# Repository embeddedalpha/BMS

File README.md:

# BMS
Battery Management System for 6s Li-ion Pack

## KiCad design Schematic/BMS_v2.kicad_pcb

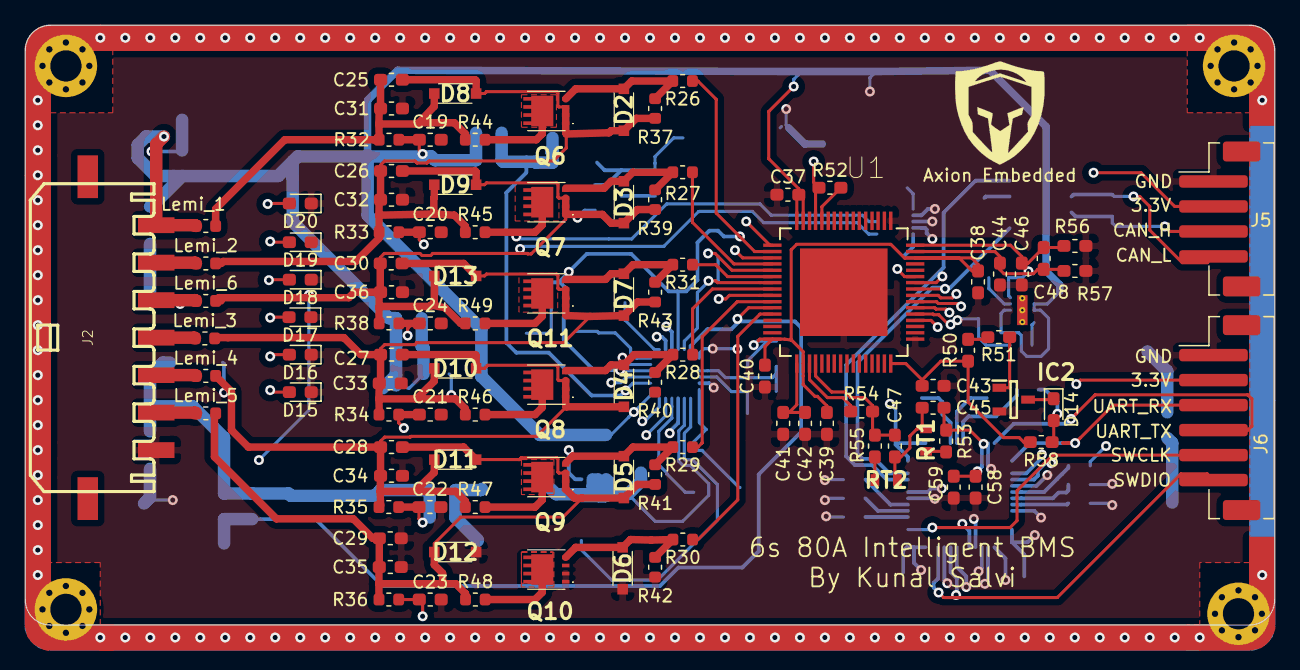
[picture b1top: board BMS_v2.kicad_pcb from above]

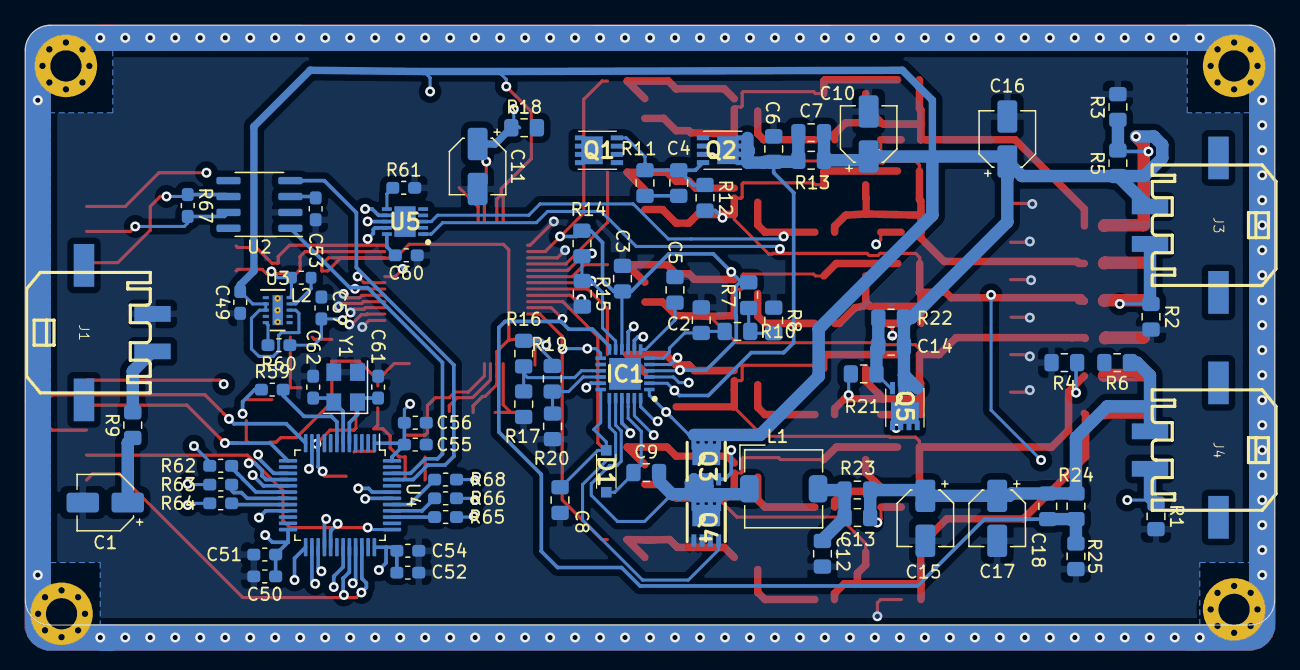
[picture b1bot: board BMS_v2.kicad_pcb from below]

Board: 4 copper layers, 100.0 x 48.0 mm, 185 parts (82 on the bottom side), 119 nets.

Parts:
C1: CP1; CP_Elec_4x3.9
C2, C7, C12, C13, C14: 0.1U; C_0805_2012Metric_Pad1.15x1.40mm_HandSolder
C3, C8: 1U; C_0805_2012Metric_Pad1.15x1.40mm_HandSolder
C4: 0.1u; C_0805_2012Metric_Pad1.15x1.40mm_HandSolder
C5: 0.056U; C_0805_2012Metric_Pad1.15x1.40mm_HandSolder
C6: C_Small; C_0805_2012Metric_Pad1.15x1.40mm_HandSolder
C9, C18: 22P; C_0805_2012Metric_Pad1.15x1.40mm_HandSolder
C10, C15, C16, C17: 10U; CP_Elec_4x3.9
C11: 1U; CP_Elec_4x3.9
C19, C20, C21, C22, C23, C24, C25, C26, C27, C28, C29, C30, C37, C39, C42, C48: 0.1U; C_0603_1608Metric_Pad1.05x0.95mm_HandSolder
C31, C32, C33, C34, C35, C36: 3300P; C_0603_1608Metric_Pad1.05x0.95mm_HandSolder
C38, C41, C43, C49, C53: 2.2U; C_0603_1608Metric_Pad1.05x0.95mm_HandSolder
C40, C45, C47: 0.047U; C_0603_1608Metric_Pad1.05x0.95mm_HandSolder
C44, C46: 1U; C_0603_1608Metric_Pad1.05x0.95mm_HandSolder
C50, C52, C55, C58: 0.47U; C_0603_1608Metric_Pad1.05x0.95mm_HandSolder
C51, C54, C56, C59, C60, C61, C62: 10N; C_0603_1608Metric_Pad1.05x0.95mm_HandSolder
C57: 22U; C_0603_1608Metric_Pad1.05x0.95mm_HandSolder
D1: D_Schottky; BZT52B5V1E308
D2, D3, D4, D5, D6, D7, D8, D9, D10, D11, D12, D13: BZT52B5V1-E3-08; BZT52B5V1E308
D14, D15, D16, D17, D18, D19, D20: LED; LED_0603_1608Metric_Pad1.05x0.95mm_HandSolder
IC1: BQ24610RGER; QFN50P400X400X100-25N-D
IC2: FDN359AN; SOT95P251X112-3N
J1: CHARGER; 43650-0212
J2: Conn_01x07; 43650-0712
J3: SYSTEM; 43650-0212
J4: BATTERY; 43650-0212
J5: Conn_01x04; JST_PH_B4B-PH-SM4-TB_1x04-1MP_P2.00mm_Vertical
J6: Conn_01x06; JST_PH_B6B-PH-SM4-TB_1x06-1MP_P2.00mm_Vertical
L1: 6.8U; L_TDK_SLF6025
L2: 6.8U; L_0603_1608Metric
Lemi_1, Lemi_2, Lemi_3, Lemi_4, Lemi_5, Lemi_6: 500; R_0603_1608Metric
Q1, Q2, Q5: SI7617DN-T1-GE3; SIS862DNT1GE3
Q3, Q4: SIS412DN-T1-GE3; POWERPAK-1212-8
Q6, Q7, Q8, Q9, Q10, Q11: CSD18543Q3AT
R1, R2, R3, R4, R5, R6: R; R_0805_2012Metric_Pad1.15x1.40mm_HandSolder
R7: 9.31K; R_0805_2012Metric_Pad1.15x1.40mm_HandSolder
R8: 430K; R_0805_2012Metric_Pad1.15x1.40mm_HandSolder
R9, R11: 100k; R_0805_2012Metric_Pad1.15x1.40mm_HandSolder
R10, R14, R15, R16, R17, R19, R20, R22, R25: 100K; R_0805_2012Metric_Pad1.15x1.40mm_HandSolder
R12, R21: 1K; R_0805_2012Metric_Pad1.15x1.40mm_HandSolder
R13: 0.01; R_0805_2012Metric_Pad1.15x1.40mm_HandSolder
R18: 10; R_0805_2012Metric_Pad1.15x1.40mm_HandSolder
R23: 0.010; R_0805_2012Metric_Pad1.15x1.40mm_HandSolder
R24: 500K; R_0805_2012Metric_Pad1.15x1.40mm_HandSolder
R26, R27, R28, R29, R30, R31, R32, R33, R34, R35, R36, R38: 1K; R_0603_1608Metric
R37, R39, R40, R41, R42, R43: 1M; R_0603_1608Metric
R44, R45, R46, R47, R48, R49: R; R_0603_1608Metric
R50: 100K; R_0603_1608Metric_Pad1.05x0.95mm_HandSolder
R51: 100; R_0603_1608Metric_Pad1.05x0.95mm_HandSolder
R52, R54: 1.82K; R_0603_1608Metric_Pad1.05x0.95mm_HandSolder
R53, R55: 1.47K; R_0603_1608Metric_Pad1.05x0.95mm_HandSolder
R56, R57: 0; R_0603_1608Metric_Pad1.05x0.95mm_HandSolder
R58: 2.7K; R_0603_1608Metric_Pad1.05x0.95mm_HandSolder
R59, R61: 100k; R_0603_1608Metric_Pad1.05x0.95mm_HandSolder
R60, R62, R63, R64, R65, R66, R68: 1K; R_0603_1608Metric_Pad1.05x0.95mm_HandSolder
R67: 120; R_0603_1608Metric_Pad1.05x0.95mm_HandSolder
RT1, RT2: NTCG163JF103FT1; THRMC1608X90N
U1: BQ76PL536A; QFP50P1200X1200X120-65N
U2: TCAN332; SOIC-8_3.9x4.9mm_P1.27mm
U3: TPS62177DQC; WSON-10-1EP_2x3mm_P0.5mm_EP0.84x2.4mm_ThermalVias
U4: STM32F103C8Tx; LQFP-48_7x7mm_P0.5mm
U5: PAC1720-1-AIA-TR; SON50P300X300X90-11N-D
Y1: 8MHz; Crystal_SMD_SeikoEpson_FA238V-4Pin_3.2x2.5mm

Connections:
+3V3: C50.1, C51.1, C52.1, C53.2, C54.1, C55.1, C56.1, C57.2, C58.1, C59.1, C60.2, J5.2, J6.2, L2.2, R59.1, R60.1, U2.3, U3.10, U4.1, U4.9, U4.24, U4.36, U4.48, U5.10
/Balance Module/ALERT: U1.38, U4.26
/Balance Module/CB1: R30.1, U1.12
/Balance Module/CB2: R29.1, U1.10
/Balance Module/CB3: R28.1, U1.8
/Balance Module/CB4: R31.1, U1.6
/Balance Module/CB5: R27.1, U1.4
/Balance Module/CB6: R26.1, U1.2
/Balance Module/CONV: U1.36, U4.27
/Balance Module/CS: U1.43, U4.29
/Balance Module/DRDY: U1.37, U4.25
/Balance Module/FAULT: U1.39, U4.28
/Balance Module/SCLK: U1.40, U4.15
/Balance Module/SDI: U1.42, U4.17
/Balance Module/SDO: U1.41, U4.16
/Balance Module/VC1: C23.1, R36.2, U1.11
/Balance Module/VC2: C22.1, R35.2, U1.9
/Balance Module/VC3: C21.1, R34.2, U1.7
/Balance Module/VC4: C24.1, R38.2, U1.5
/Balance Module/VC5: C20.1, R33.2, U1.3
/Balance Module/VC6: C19.1, R32.2, U1.1
/Cell_AFE/BAT1: J2.2, Lemi_5.1
/Cell_AFE/BAT2: J2.3, Lemi_4.1
/Cell_AFE/BAT3: J2.4, Lemi_3.1
/Cell_AFE/BAT4: J2.5, Lemi_6.1
/Cell_AFE/BAT5: J2.6, Lemi_2.1
/Charger/PG: IC1.8, U4.31
/Charger/Power_IN: J1.1, Q1.5, Q1.6, Q1.7, Q1.8, R9.2
/Charger/STAT1: IC1.5, U4.32
/Charger/STAT2: IC1.9, U4.33
/Charger/THERMO: R7.1, R8.2, R10.1
/Controller/BAT_R_+: J4.2, R1.1, U5.3
/Controller/BAT_V: R4.1, R6.2, U4.10
/Controller/SYS_R_+: J3.2, R2.1, U5.1
/Controller/SYS_V: R3.1, R5.2, U4.11
ACDRV: IC1.3, R12.2
ACN: C7.1, C10.1, C13.1, C14.2, C15.1, C16.1, C17.1, C18.2, C37.2, C49.2, IC1.1, IC1.13, J2.7, J3.1, J4.1, Lemi_1.1, Q3.5, Q3.6, Q3.7, Q3.8, Q5.1, Q5.2, Q5.3, Q5.5, Q5.6, Q5.7, Q5.8, R5.1, R6.1, R13.1, R22.2, R23.1, R24.2, U1.63, U1.64, U3.2, U3.3, U3.8
ACP: C6.2, C7.2, IC1.2, IC1.17, Q2.5, Q2.6, Q2.7, Q2.8, R13.2
ACSET: IC1.16, R19.2, R20.1
BATDRV: IC1.23, R21.2
BTST: C9.1, D1.1, IC1.22
CANRX: U2.4, U4.45
CANTX: U2.1, U4.46
CAN_H: J5.3, R67.2, U2.7
CAN_L: J5.4, R67.1, U2.6
CE: C3.1, C38.2, C39.2, C40.2, IC1.4, IC1.10, R7.2, R14.1, R16.1, R19.1, U1.16, U1.18, U1.46
GND: C1.2, C2.2, C3.2, C5.2, C6.1, C8.2, C10.2, C11.2, C12.2, C15.2, C16.2, C17.2, C19.2, C20.2, C21.2, C22.2, C23.2, C24.2, C29.2, C31.2, C32.2, C33.2, C34.2, C35.2, C36.2, C37.1, C38.1, C39.1, C40.1, C41.1, C42.1, C43.2, C44.2, C46.2, C49.1, C50.2, C51.2, C52.2, C53.1, C54.2, C55.2, C56.2, C57.1, C58.2, C59.2, C60.1, C61.2, C62.2, D6.2, D12.2, D15.1, D16.1, D17.1, D18.1, D19.1, D20.1, IC2.2, J1.2, J2.1, J5.1, J6.1, Q4.1, Q4.2, Q4.3, Q10.1, Q10.2, Q10.3, R1.2, R2.2, R3.2, R4.2, R8.1, R15.2, R17.2, R20.2, R25.1, R42.1, R56.1, R57.1, R61.2, U1.13, U1.14, U1.15, U1.25, U1.33, U1.34, U1.35, U1.44, U1.49, U1.50, U1.65, U2.2, U3.1, U3.4, U3.6, U3.7, U3.11, U4.8, U4.23, U4.35, U4.44, U4.47, U5.2, U5.4, U5.5, U5.11, Y1.2, Y1.3
GPAI+: C46.1, C48.1, R56.2, U1.48
GPAI-: C44.1, C48.2, R57.2, U1.47
GPIO: R50.2, R51.1, U1.45
HIDRV: IC1.21, Q3.4
I2C_ALERT: U4.21, U5.7
I2C_SCL: U4.42, U5.9
I2C_SDA: U4.43, U5.8
ISET1: IC1.11, R14.2, R15.1
ISET2: IC1.15, R16.2, R17.1
LDOA: C41.2, C42.2, U1.17
LED1: R62.2, U4.18
LED2: R63.2, U4.19
LED3: R64.2, U4.20
LED4: R65.2, U4.39
LED5: R66.2, U4.40
LED6: R68.2, U4.41
LODRV: IC1.19, Q4.4
unnamed: C1.1, R9.1
unnamed: C4.1, Q1.4, Q2.4, R11.1, R12.1
unnamed: C4.2, Q1.1, Q1.2, Q1.3, Q2.1, Q2.2, Q2.3, R11.2, R18.2
unnamed: C14.1, Q5.4, R21.1, R22.1
unnamed: C25.1, C31.1, D8.1, Lemi_1.2, R32.1, R44.1
unnamed: C25.2, C26.1, C32.1, D2.2, D8.2, D9.1, Lemi_2.2, Q6.1, Q6.2, Q6.3, R33.1, R37.1, R45.1
unnamed: C26.2, C30.1, C36.1, D3.2, D9.2, D13.1, Lemi_6.2, Q7.1, Q7.2, Q7.3, R38.1, R39.1, R49.1
unnamed: C27.1, C30.2, C33.1, D7.2, D10.1, D13.2, Lemi_3.2, Q11.1, Q11.2, Q11.3, R34.1, R43.1, R46.1
unnamed: C27.2, C28.1, C34.1, D4.2, D10.2, D11.1, Lemi_4.2, Q8.1, Q8.2, Q8.3, R35.1, R40.1, R47.1
unnamed: C28.2, C29.1, C35.1, D5.2, D11.2, D12.1, Lemi_5.2, Q9.1, Q9.2, Q9.3, R36.1, R41.1, R48.1
unnamed: D2.1, Q6.4, R26.2, R37.2
unnamed: D3.1, Q7.4, R27.2, R39.2
unnamed: D4.1, Q8.4, R28.2, R40.2
unnamed: D5.1, Q9.4, R29.2, R41.2
unnamed: D6.1, Q10.4, R30.2, R42.2
unnamed: D7.1, Q11.4, R31.2, R43.2
unnamed: D14.1, IC2.3
unnamed: D14.2, R58.1
unnamed: D15.2, R62.1
unnamed: D16.2, R63.1
unnamed: D17.2, R64.1
unnamed: D18.2, R65.1
unnamed: D19.2, R66.1
unnamed: D20.2, R68.1
unnamed: IC2.1, R51.2
unnamed: L2.1, U3.9
unnamed: Q6.5, Q6.6, Q6.7, Q6.8, Q6.9, R44.2
unnamed: Q7.5, Q7.6, Q7.7, Q7.8, Q7.9, R45.2
unnamed: Q8.5, Q8.6, Q8.7, Q8.8, Q8.9, R46.2
unnamed: Q9.5, Q9.6, Q9.7, Q9.8, Q9.9, R47.2
unnamed: Q10.5, Q10.6, Q10.7, Q10.8, Q10.9, R48.2
unnamed: Q11.5, Q11.6, Q11.7, Q11.8, Q11.9, R49.2
unnamed: R53.1, RT1.2
unnamed: R55.1, RT2.2
unnamed: R59.2, U4.7
unnamed: R60.2, U3.5
unnamed: R61.1, U5.6
OSC_IN: C61.1, U4.5, Y1.1
OSC_OUT: C62.1, U4.6, Y1.4
PH: C9.2, IC1.20, L1.1, Q3.1, Q3.2, Q3.3, Q4.5, Q4.6, Q4.7, Q4.8
REG50: C43.1, C45.1, C47.1, R50.1, R58.2, RT1.1, RT2.1, U1.32
REGN: C8.1, D1.2, IC1.18
SRP: C12.1, C13.2, IC1.14, L1.2, R23.2
SWCLK: J6.5, U4.37
SWDIO: J6.6, U4.34
TS: C2.1, IC1.6, R10.2
TS1+: C47.2, R54.1, R55.2, U1.20
TS1-: R54.2, U1.19
TS2+: C45.2, R52.1, R53.2, U1.61
TS2-: R52.2, U1.60
TTC: C5.1, IC1.7
UART_RX: J6.3, U4.13
UART_TX: J6.4, U4.12
VCC: C11.1, IC1.24, R18.1
VFB: C18.1, IC1.12, R24.1, R25.2

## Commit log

2020-07-02 Add files via upload
    Deleted a few redundant files. Refined protection and balancing part.
